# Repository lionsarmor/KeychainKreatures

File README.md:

# Keychain Kreatures

An ESP32-S3 virtual-pet and small handheld-game hardware project, designed around a repairable through-hole main-board kit and a separate factory-assembled power board.

**Current hardware: main C.6 + power P.4. Engineering prototypes—not a tested, certified or production-ready toy.** Main is 96 × 105 × 1.6 mm; power is now 50 × 50 × 1.6 mm. The power board needs independent removable case supports; mounting patterns do not match. Physical component fit, battery/case selection, factory DFM approval and powered qualification remain open.

## Current projects and downloads

| Board | Editable KiCad 10 project | Five-prototype review package | Gerbers and drills |
|---|---|---|---|
| Main C.6 · 2 copper layers | [Open main project](KK_main_module/KK_main_module.kicad_pro) | [Full main ZIP](KK_main_module/manufacturing/KK_MAIN_C6_P4_PAIRING_5_PROTOTYPE_REVIEW_2026-09-12.zip) | [Main fabrication ZIP](KK_main_module/manufacturing/KK_MAIN_C6_P4_PAIRING_GERBERS.zip) |
| Power P.4 · 4 copper layers | [Open power project](KK_power_module/KK_power_module.kicad_pro) | [Full power ZIP](KK_power_module/manufacturing/KK_POWER_P4_5_PROTOTYPE_REVIEW_2026-09-12.zip) | [Power fabrication ZIP](KK_power_module/manufacturing/KK_POWER_P4_GERBERS.zip) |

Download the repository or a **full review ZIP** to open a project with its local libraries, models and documentation. Install the KiCad 10 standard footprint and 3D libraries as well. For GitHub ZIP downloads, use the file page's download/raw action. The full review packages include fabrication files, BOMs, placement and test-point maps, schematic/assembly PDFs, source CAD, datasheets and verification evidence. The separate fabrication ZIPs do not replace the assembler's full review package.

[Start here](START_HERE.md) · [Documentation index](docs/README.md) · [Release notes](CHANGELOG.md) · [Release hashes](docs/CURRENT_RELEASE_INDEX.json)

Ordering the five engineering samples? Use the [PCBWay step-by-step submission folder](PCBWay/README.md): separate main/power Gerber uploads, power BOM/centroid, DFM questions, approval checklist and delivery/testing documents. This is a local preparation packet, not an order or manufacturing approval.

## Hardware in this revision

- Socketed **ESP32-S3 SuperMini**. Confirm the delivered seller revision, pinout and actual flash/PSRAM; do not infer N16R8 specifications from the SuperMini name.
- Existing ST7789V2 screen in landscape, **280 × 240 pixels**, and a separate socketed 3.3 V microSD reader. SD storage is not extra executable RAM.
- Nine soft controls: D-pad left, four action buttons right, one center function button, all below the screen. MCP23017 GPIO expansion.
- PWM audio with a TDA2822L amplifier, speaker connector and switched amplifier supply; vibration motor output with suppression.
- TSAL6200 infrared transmitter and TSOP38238 receiver, aimed toward the case opening. No sub-GHz radio.
- Separate socketed common-anode RGB LED and TLC5916 driver.
- Main board: **98 fitted through-hole positions**, all **43 resistors horizontal**, ten horizontal low-profile electrolytics, six flat-mounted TO-92 devices, removable IC/module sockets, JST connectors and **25 bare debug holes**.
- Power board: **108 fitted positions**, 28 rear test pads, USB-C charging input, battery protection, temperature interlock and three regulated output rails. This board is a **factory SMT subassembly**, not a student SMT soldering exercise.

All fitted electrical positions have resolving 3D model links. Some module and connector envelopes remain provisional; model coverage does not prove fit. Sockets, buttons and optical components necessarily retain height. The previous common-hole 20 mm spacer plan is superseded. Power placement, antenna clearance and independent support heights need a physical mock-up.

## Assembly and first power-up

New to electronics, or investigating a board that will not start? Use the [board-by-board troubleshooting guides and recording sheets](docs/troubleshooting/README.md). Begin with safety and unpowered checks; power-module live tests need a qualified instructor.

Read these before buying parts, soldering or powering a board:

1. [Main BOM and assembly/wiring guide](KK_main_module/assembly/ASSEMBLY_GUIDE.md), [reference BOM](KK_main_module/assembly/C6_BOM_BY_REFERENCE.csv), and [complete paired-kit extras](KK_main_module/assembly/C6_COMPLETE_KIT_EXTRAS.csv). Extras cover sockets, modules, mating plugs, wiring and provisional hardware; count them once per main+power pair.
2. [Print the stack review at actual size](docs/C6_P4_MECHANICAL_REVIEW.pdf), [front fit sheet](KK_main_module/assembly/C6_front_FIT_100_PERCENT.pdf) and [rear fit sheet](KK_main_module/assembly/C6_back_FIT_100_PERCENT.pdf). Measure the calibration line and dry-fit actual parts and plugged harnesses.
3. [Power fabrication/assembly requirements](KK_power_module/FABRICATION_REQUIREMENTS.md). Obtain manufacturer approval of the 0.4 mm WCSP, fine-pitch packages and **filled/capped/planarized via-in-pad** process. Ordinary via tenting is not equivalent.
4. [Power electrical review and current-limited first-power-up procedure](KK_power_module/assembly/P4_REVIEW_AND_TEST.md). Qualify power independently before attaching the populated main board. Real-cell testing requires a selected, documented cell and bonded thermistor.

Power **J3 → main J1**, keyed pin-for-pin:

| Pin | Rail |
|---|---|
| 1 | MCU_5V |
| 2 | GND |
| 3 | LOGIC_3V3 |
| 4 | ACT_3V2 |

**Never connect raw battery voltage to main J1. Power TP3/BAT_NEG is not TP4/GND; do not bypass battery protection with test-equipment grounds. Neither speaker output is ground.**

Charger USB carries **no data** to the ESP32. Do not combine ESP32 USB power and external main rails until exact-module reverse-feed behavior is qualified. Program the removable MCU separately for recovery. USB-A/default charging is deliberately slow and may not cover a running toy's load.

## Verification and remaining work

The issued C.6/P.4 sources passed fresh native ERC/DRC, connectivity and schematic-parity checks with **zero reported violations or opens**. [Static audit](docs/CURRENT_STATIC_AUDIT.json), [individual outline/hole audit](docs/CURRENT_STATIC_AUDIT.json) and package manifests identify exactly what was checked. Existing ignored-check settings are included in the native reports; clean reports are not a claim that every possible check was performed.

Run this lightweight saved-release consistency check from the repository root:

```sh
node tools/check_project.mjs
```

It verifies current source/package hashes, local assets, saved netlists and the inter-board interface. It does **not** rerun KiCad checks or simulate the circuit. See [tool instructions](tools/README.md) before running anything else. Do not rerun historical placement/route generators on finished CAD.

Remaining qualification includes physical socket/plug/case fit, battery/NTC selection, speaker power rating, simultaneous-load capacity, capacitor transient/ripple behavior, regulator/charger temperatures, USB behavior, rail sequencing, GPIO back-powering, RF performance and applicable product safety/EMC review. In particular, the older main 3.3 V reservation was 0.5 A while power screening used 0.4 A; reconcile measured peak demand and margin before approving the complete toy. Screening targets are not measured ratings.

## Firmware status

The planned virtual pet, games/apps, browser/Wi-Fi uploads, trading, save recovery and OTA workflow are **not implemented or validated by this hardware release**. Follow the current schematic and assembly guide for bring-up firmware. The historical ESP32-C3/MAX98357A/PCF8574 test sketch from earlier Git history is not compatible with this S3/MCP23017/TDA2822L board and must not be used as its factory test.

## History, contributions and licensing

The files directly inside **KK_main_module are now C.6**, and those directly inside **KK_power_module are P.4**. Older C.5/P.2 projects, intermediate routes, obsolete documents and one-off generators have been moved into [the cleanup archive](revisions/2026-09-12_current_only/). Use [revisions](revisions/README.md) for recovery; archived reports retain their original findings and are not current instructions. See [contribution guidance](CONTRIBUTING.md).

The project is intended for open development, but a project-wide license has **not yet been selected**. The OSHW silkscreen logo is not a certification or a substitute for license terms. Third-party KiCad assets and manufacturer documents retain their respective terms; do not assume this repository relicenses them. Thanks to the KiCad, Espressif and component-library communities.

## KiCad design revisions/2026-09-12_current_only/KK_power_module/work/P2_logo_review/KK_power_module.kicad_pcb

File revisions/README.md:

# Historical revisions — do not manufacture from here

The [2026-09-11 cleanup archive](2026-09-11_cleanup/) preserves the original relative project paths. No archived design is the current project.

- `KK_power_module/`: legacy two-wire power board, P.1, previous backups, old fabrication outputs and original engineering scripts.
- `KK_power_module/P2_compact/`: abandoned P.2 routing candidates and intermediate board snapshots. These routes were not imported or qualified.
- `KK_main_module/`: superseded reports, BOMs, routing candidates, older schematic capture, backups and former archives.

The current projects remain outside this directory; open them through [START_HERE.md](../START_HERE.md).

## Current-only folder cleanup

[2026-09-12_current_only](2026-09-12_current_only/) holds the former C.5 main root, C5_relayout, P2_compact, old main assembly/component investigations, intermediate C.6 routes, historical documents and one-off generators. [MOVE_MANIFEST.json](2026-09-12_current_only/MOVE_MANIFEST.json) records each move and protected current CAD/ZIP hashes. Active C.6/P.3 now sit directly in their module folders.

Archived relative compatibility symlinks preserve their original text and may not resolve from their new archive location. Recover a historical project into a separate scratch tree using the manifest; do not copy it over current CAD. No material content was deleted.

## C.6 / P.3 release archive

[2026-09-12_C6_P3_release](2026-09-12_C6_P3_release/) preserves the superseded C.5/P.2 manufacturing directories, ZIPs and reports, plus the previous Desktop print sheet and the C.6/P.3 preflight ZIPs before final documentation cleanup. None of those ZIPs is the current release. [MOVE_MANIFEST.json](2026-09-12_C6_P3_release/MOVE_MANIFEST.json) distinguishes moves from preserved copies and records exact hashes. No baseline CAD was deleted or overwritten.

## Recovery

[MOVE_MANIFEST.json](2026-09-11_cleanup/MOVE_MANIFEST.json) records each original path, new path and per-file SHA-256 hash. Every move was verified. Active CAD/library/model hashes were checked separately to establish that cleanup did not modify them. Nothing was deleted.

For recovery, copy the desired archived files to a **separate scratch project**, preserving their recorded original relative paths. Include corresponding libraries/models and any generator inputs. Do not overwrite the current projects. Archived generation scripts retain original paths and are historical source, not working commands in their relocated tree. Never run them over current CAD.

The former compatibility symlinks at `KK_main_module/archive`, `KK_main_module/pcb/backups` and `KK_main_module/schematic` are now archived too. Historical reports may contain obsolete links; the move manifests, not the old links, are the recovery map.

The archive may contain packages named `FACTORY` or `release`. Those names are historical and do not approve them for the present main board, battery or product.

## Compact power P.4

See [2026-09-12_power_compact](2026-09-12_power_compact/) for the preserved P.3 projects, prior packages, source snapshots and promotion hash map. Current power is 50 × 50 mm with separate mounts; main C.6 remains unchanged.

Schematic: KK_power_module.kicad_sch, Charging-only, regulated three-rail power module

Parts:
C1, C71, C72: 1u; C_0603_1608Metric; MPN GRM188R71C105KA12D
C2, C6, C9, C25, C35, C45, C51, C60, C70: 100n; C_0603_1608Metric; MPN GRM188R71C104KA01D
C3: 4.7u; C_0805_2012Metric; MPN GRM21BR71C475KA73L
C4, C20, C21, C30, C31, C40, C41: 10u; C_0805_2012Metric; MPN GRM21BR61C106KE15L
C5, C8, C22, C23, C24, C32, C33, C34, C42, C43, C44: 22u; C_0805_2012Metric; MPN GRM21BR61C226ME44L
C7, C52, C53, C54: 10n; C_0603_1608Metric; MPN GRM188R71H103KA01D
C28, C38, C48: 10p; C_0603_1608Metric; MPN GRM1885C1H100JA01D
D1: SMAJ5.0A; D_SMA; MPN SMAJ5.0A
F1: 4A FAST; Fuse_1206_3216Metric; MPN 0451004.MRL
J1: USB-C CHARGE ONLY; USB_C_HCTL; MPN HC-TYPE-C-16P-01A
J2: 1S CELL / VH; JST_VH_B2P-VH_1x02_P3.96mm_Vertical; MPN B2P-VH(LF)(SN)
J3: C.5 SYS_IN / XH; JST_XH_B4B-XH-A_1x04_P2.50mm_Vertical; MPN B4B-XH-A(LF)(SN)
J4: BATTERY NTC; JST_PH_B2B-PH-K_1x02_P2.00mm_Vertical; MPN B2B-PH-K-S(LF)(SN)
L1, L2, L3: 1uH; L_Coilcraft_XxL4020; MPN XFL4020-102MEC
LED1: POWER GOOD; LED_1206_3216Metric; MPN APT3216LZGCK
LED2: CHARGING; LED_1206_3216Metric; MPN APT3216SURCK
Q1, Q2, Q3: FS8205; MPN FS8205
Q4, Q5: AO3400A; SOT-23; MPN AO3400A
R1: 887k; R_0603_1608Metric; MPN RC0603FR07887KL
R2, R6, R7: 4.7k; R_0603_1608Metric; MPN RC0603FR074K7L
R3, R14, R60: 10k; R_0603_1608Metric; MPN RC0603FR0710KL
R4: 2.94k; R_0603_1608Metric; MPN RT0603BRD072K94L
R5: 1.3k; R_0603_1608Metric; MPN RC0603FR071K3L
R8: 470; R_0603_1608Metric; MPN RC0603FR07470RL
R9: 1k; R_0603_1608Metric; MPN RC0603FR071KL
R10: 182k; R_0603_1608Metric; MPN RT0603BRD07182KL
R11, R31, R41, R62, R64, R66: 100k; R_0603_1608Metric; MPN RT0603BRD07100KL
R12: 620; R_0603_1608Metric; MPN RC0603FR07620RL
R13, R51, R72, R73: 100k; R_0603_1608Metric; MPN RC0603FR07100KL
R20: 909k; R_0603_1608Metric; MPN RT0603BRD07909KL
R21: 101k; R_0603_1608Metric; MPN RT0603BRD07101KL
R30: 560k; R_0603_1608Metric; MPN RT0603BRD07560KL
R40, R43: 270k; R_0603_1608Metric; MPN RT0603BRD07270KL
R50: 470k; R_0603_1608Metric; MPN RC0603FR07470KL
R52, R53, R54: 100; R_0603_1608Metric; MPN RC0603FR07100RL
R61: 1060k; R_0603_1608Metric; MPN RT0603BRD071M06L
R63: 665k; R_0603_1608Metric; MPN RT0603BRD07665KL
R65: 649k; R_0603_1608Metric; MPN RT0603BRD07649KL
R70: 19.2k; R_0603_1608Metric; MPN RT0603BRD0719K2L
R71: 634; R_0603_1608Metric; MPN RT0603BRD07634RL
R74: 31.6k; R_0603_1608Metric; MPN RT0603BRD0731K6L
R75: 20k; R_0603_1608Metric; MPN RT0603BRD0720KL
SW1: OFF / ON; SW_SPDT_CK_JS102011SAQN; MPN JS102011SAQN
TP1: VBUS; TestPoint_Pad_D1.5mm; MPN BARE PCB PAD
TP2: VBAT; TestPoint_Pad_D1.5mm; MPN BARE PCB PAD
TP3: BAT_NEG; TestPoint_Pad_D1.5mm; MPN BARE PCB PAD
TP4: GND; TestPoint_Pad_D1.5mm; MPN BARE PCB PAD
TP5: SYS_RAW; TestPoint_Pad_D1.5mm; MPN BARE PCB PAD
TP6: SYS_SW; TestPoint_Pad_D1.5mm; MPN BARE PCB PAD
TP7: RUN_CTL; TestPoint_Pad_D1.5mm; MPN BARE PCB PAD
TP8: EF_UVLO; TestPoint_Pad_D1.5mm; MPN BARE PCB PAD
TP9: EF_ILIM; TestPoint_Pad_D1.5mm; MPN BARE PCB PAD
TP10: EF_FAULT_N; TestPoint_Pad_D1.5mm; MPN BARE PCB PAD
TP11: PG_ALL; TestPoint_Pad_D1.5mm; MPN BARE PCB PAD
TP12: RAILS_EN; TestPoint_Pad_D1.5mm; MPN BARE PCB PAD
TP13: REG_5V; TestPoint_Pad_D1.5mm; MPN BARE PCB PAD
TP14: REG_3V3; TestPoint_Pad_D1.5mm; MPN BARE PCB PAD
TP15: REG_3V2; TestPoint_Pad_D1.5mm; MPN BARE PCB PAD
TP16: MCU_5V; TestPoint_Pad_D1.5mm; MPN BARE PCB PAD
TP17: LOGIC_3V3; TestPoint_Pad_D1.5mm; MPN BARE PCB PAD
TP18: ACT_3V2; TestPoint_Pad_D1.5mm; MPN BARE PCB PAD
TP19: NTC; TestPoint_Pad_D1.5mm; MPN BARE PCB PAD
TP20: CC_DEFAULT_N; TestPoint_Pad_D1.5mm; MPN BARE PCB PAD
TP21: USB_HIGH_CURRENT; TestPoint_Pad_D1.5mm; MPN BARE PCB PAD
TP22: USB_CHG; TestPoint_Pad_D1.5mm; MPN BARE PCB PAD
TP23: USB_PORT_ILIM; TestPoint_Pad_D1.5mm; MPN BARE PCB PAD
TP24: USB_LIMIT_FAULT_N; TestPoint_Pad_D1.5mm; MPN BARE PCB PAD
TP25: CC_3V3; TestPoint_Pad_D1.5mm; MPN BARE PCB PAD
TP26: PGOOD_N; TestPoint_Pad_D1.5mm; MPN BARE PCB PAD
TP27: CHARGE_N; TestPoint_Pad_D1.5mm; MPN BARE PCB PAD
TP28: VOLTAGES_OK; TestPoint_Pad_D1.5mm; MPN BARE PCB PAD
U1: BQ24075TRGTR; VQFN-16-1EP_3x3mm_P0.5mm_EP1.6x1.6mm; MPN BQ24075TRGTR
U2: DW01A / H&M; SOT-23-6; MPN DW01A
U3: TUSB320LAIRWBR; Texas_X2QFN-12_1.6x1.6mm_P0.4mm; MPN TUSB320LAIRWBR
U4: TPS259530DSGR; Texas_DSG0008A_WSON-8-1EP_2x2mm_P0.5mm_EP0.9x1.6mm; MPN TPS259530DSGR
U5, U6, U7: TPS63060DSCR; Texas_S-PWSON-N10; MPN TPS63060DSCR
U8, U9, U10: TPS22918DBVR; SOT-23-6; MPN TPS22918DBVR
U11: SN74AUP1G17DBVR; SOT-23-5; MPN SN74AUP1G17DBVR
U12: TPS386000RGPR; Texas_RGP0020D_VQFN-20-1EP_4x4mm_P0.5mm_EP2.7x2.7mm; MPN TPS386000RGPR
U13: TPS22950YBHR; TPS22950_YBH; MPN TPS22950YBHR
U14: TLV75533PDBVR; SOT-23-5; MPN TLV75533PDBVR

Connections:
/ACT_3V2: J3.4 (3V2), R54.1, TP18.1, U10.6 (VOUT)
/BAT_NEG: C6.2, J2.2 (CELL-), Q1.1 (S1), Q2.1 (S1), Q3.1 (S1), TP3.1, U2.6 (GND)
/CC1: J1.A5 (CC1), U3.1 (CC1)
/CC2: J1.B5 (CC2), U3.2 (CC2)
/CC_3V3: C2.1, C72.1, R2.1, R3.1, TP25.1, U3.12 (VDD), U14.5 (OUT)
/CC_DEFAULT_N: Q4.1 (G), R2.2, TP20.1, U3.7 (OUT1)
/CELL_PLUS: F1.1, J2.1 (CELL+)
/CHARGE_N: R7.2, TP27.1, U1.9 (~CHG)
/CHG_ILIM: R5.1, U1.12 (ILIM)
/CHG_ISET: R4.1, U1.16 (ISET)
/DRAIN_COMMON: Q1.2 (D1), Q1.5 (D2), Q2.2 (D1), Q2.5 (D2), Q3.2 (D1), Q3.5 (D2)
/EF_FAULT_N: R13.2, TP10.1, U4.6 (FAULT_N)
/EF_ILIM: R12.1, TP9.1, U4.7 (ILM)
/EF_SLEW: C7.1, U4.1 (dVdt)
/EF_UVLO: R10.2, R11.1, TP8.1, U4.2 (EN / UVLO)
/GND: C1.2, C2.2, C3.2, C4.2, C5.2, C7.2, C8.2, C9.2, C20.2, C21.2, C22.2, C23.2, C24.2, C25.2, C28.2, C30.2, C31.2, C32.2, C33.2, C34.2, C35.2, C38.2, C40.2, C41.2, C42.2, C43.2, C44.2, C45.2, C48.2, C51.2, C52.2, C53.2, C54.2, C60.2, C70.2, C71.2, C72.2, D1.2 (A), J1.A1 (GND), J1.A12 (GND), J1.B1 (GND), J1.B12 (GND), J1.S1 (SHIELD), J3.2 (GND), J4.2 (GND), Q1.3 (S2), Q2.3 (S2), Q3.3 (S2), Q4.2 (S), Q5.2 (S), R4.2, R5.2, R9.1, R11.2, R12.2, R21.2, R31.2, R41.2, R51.2, R62.2, R64.2, R66.2, R70.2, R72.2, R75.2, SW1.1 (A), TP4.1, U1.4 (~CE), U1.6 (EN1), U1.8 (VSS), U1.15 (SYSOFF), U1.17 (VSS), U3.3 (PORT = SINK), U3.10 (GND), U3.11 (EN_N), U4.8 (GND), U4.9 (EP / GND), U5.7 (GND), U5.11 (PGND), U6.7 (GND), U6.11 (PGND), U7.7 (GND), U7.11 (PGND), U8.2 (GND), U9.2 (GND), U10.2 (GND), U11.3 (GND), U12.6 (SENSE4H), U12.11 (NC / GND), U12.12 (GND), U12.20 (WDI), U12.21 (EP / GND), U13.C1 (GND), U14.2 (GND)
/LED1_K: LED1.1 (K), R6.1
/LED2_K: LED2.1 (K), R7.1
/LOGIC_3V3: J3.3 (3V3), R53.1, TP17.1, U9.6 (VOUT)
/MCU_5V: J3.1 (5V), R52.1, TP16.1, U8.6 (VOUT)
/NTC: J4.1 (NTC), R74.2, R75.1, TP19.1, U1.1 (TS)
/OC: Q1.4 (G2 / OC), Q2.4 (G2 / OC), Q3.4 (G2 / OC), U2.3 (OC)
/OD: Q1.6 (G1 / OD), Q2.6 (G1 / OD), Q3.6 (G1 / OD), U2.1 (OD)
/PGOOD_N: R6.2, TP26.1, U1.7 (~PGOOD)
/PG_ALL: R50.2, TP11.1, U5.5 (PG), U6.5 (PG), U7.5 (PG)
/PROTECT_CS: R9.2, U2.2 (CS)
/PROTECT_VCC: C6.1, R8.2, U2.5 (VCC)
/RAILS_EN: R51.1, TP12.1, U8.3 (ON), U9.3 (ON), U10.3 (ON), U11.4 (Y)
/REG_3V2: C42.1, C43.1, C44.1, R40.1, R65.1, TP15.1, U7.9 (VOUT), U10.1 (VIN)
/REG_3V3: C32.1, C33.1, C34.1, C51.1, R30.1, R50.1, R60.1, R63.1, TP14.1, U6.9 (VOUT), U9.1 (VIN), U11.5 (VCC)
/REG_5V: C22.1, C23.1, C24.1, R20.1, R61.1, TP13.1, U5.9 (VOUT), U8.1 (VIN)
/REG_ENABLE: R14.2, U5.3 (EN), U5.4 (PS/SYNC), U6.3 (EN), U6.4 (PS/SYNC), U7.3 (EN), U7.4 (PS/SYNC)
/RUN_CTL: R10.1, R14.1, SW1.2 (B), TP7.1, U12.1 (MR_N)
/SENSE_3V2: R65.2, R66.1, U12.8 (SENSE3)
/SENSE_3V3: R63.2, R64.1, U12.9 (SENSE2)
/SENSE_5V: R61.2, R62.1, U12.10 (SENSE1)
/SYS_RAW: C5.1, C9.1, C60.1, R13.1, SW1.3 (C), TP5.1, U1.10 (OUT), U1.11 (OUT), U4.3 (IN), U4.4 (IN), U12.14 (VDD)
/SYS_SW: C8.1, C20.1, C21.1, C30.1, C31.1, C40.1, C41.1, TP6.1, U4.5 (OUT), U5.2 (VIN), U6.2 (VIN), U7.2 (VIN), U12.7 (SENSE4L)
/U5_AUX: C25.1, U5.6 (VAUX)
/U5_FB: C28.1, R20.2, R21.1, U5.8 (FB)
/U5_L1: L1.1, U5.1 (L1)
/U5_L2: L1.2, U5.10 (L2)
/U6_AUX: C35.1, U6.6 (VAUX)
/U6_FB: C38.1, R30.2, R31.1, U6.8 (FB)
/U6_L1: L2.1, U6.1 (L1)
/U6_L2: L2.2, U6.10 (L2)
/U7_AUX: C45.1, U7.6 (VAUX)
/U7_FB: C48.1, R41.1, R43.2, U7.8 (FB)
/U7_FB_MID: R40.2, R43.1
/U7_L1: L3.1, U7.1 (L1)
/U7_L2: L3.2, U7.10 (L2)
/U8_CT: C52.1, U8.4 (CT)
/U8_QOD: R52.2, U8.5 (QOD)
/U9_CT: C53.1, U9.4 (CT)
/U9_QOD: R53.2, U9.5 (QOD)
/U10_CT: C54.1, U10.4 (CT)
/U10_QOD: R54.2, U10.5 (QOD)
/USB_CHG: C3.1, C71.1, R74.1, TP22.1, U1.13 (IN), U13.B2 (VOUT)
/USB_HIGH_CURRENT: Q4.3 (D), Q5.1 (G), R3.2, R72.1, TP21.1, U1.5 (EN2)
/USB_LIMIT_FAULT_N: R73.2, TP24.1, U13.A2 (FLT_N)
/USB_PORT_ILIM: R70.1, R71.1, TP23.1, U13.C2 (ILIM)
/USB_PORT_ILIM_FAST: Q5.3 (D), R71.2
/VBAT: C4.1, F1.2, R8.1, TP2.1, U1.2 (BAT), U1.3 (BAT)
/VBUS: C1.1, C70.1, D1.1 (K), J1.A4 (VBUS), J1.A9 (VBUS), J1.B4 (VBUS), J1.B9 (VBUS), LED1.2 (A), LED2.2 (A), R1.1, R73.1, TP1.1, U13.A1 (ON), U13.B1 (VIN), U14.1 (IN), U14.3 (EN)
/VBUS_DET: R1.2, U3.4 (VBUS_DET)
/VOLTAGES_OK: R60.2, TP28.1, U11.2 (A), U12.15 (RESET1_N), U12.16 (RESET2_N), U12.17 (RESET3_N)

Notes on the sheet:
USB-C CHARGING ONLY
CELL CHARGER / POWER PATH
CELL PROTECTION / FUSE
SYSTEM SWITCH / INRUSH / UVLO
5 V BUCK-BOOST
3.3 V BUCK-BOOST
3.2 V BUCK-BOOST
ALL-RAIL READY / SOFT OUTPUTS
VOLTAGE SUPERVISION / STARTUP
USB-A / USB-C INPUT CURRENT
MAIN BOARD HARNESS / DEBUG
KEYCHAIN KREATURES / POWER P.2 - ENGINEERING, NOT RELEASED

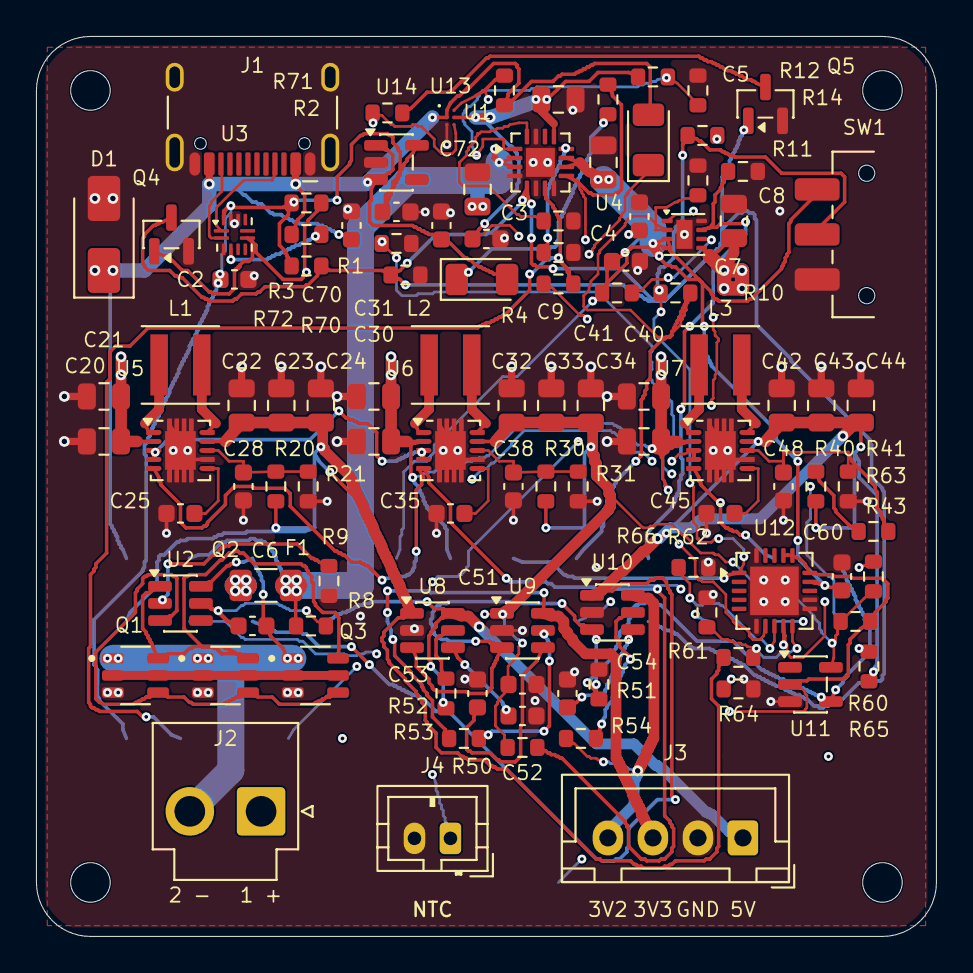
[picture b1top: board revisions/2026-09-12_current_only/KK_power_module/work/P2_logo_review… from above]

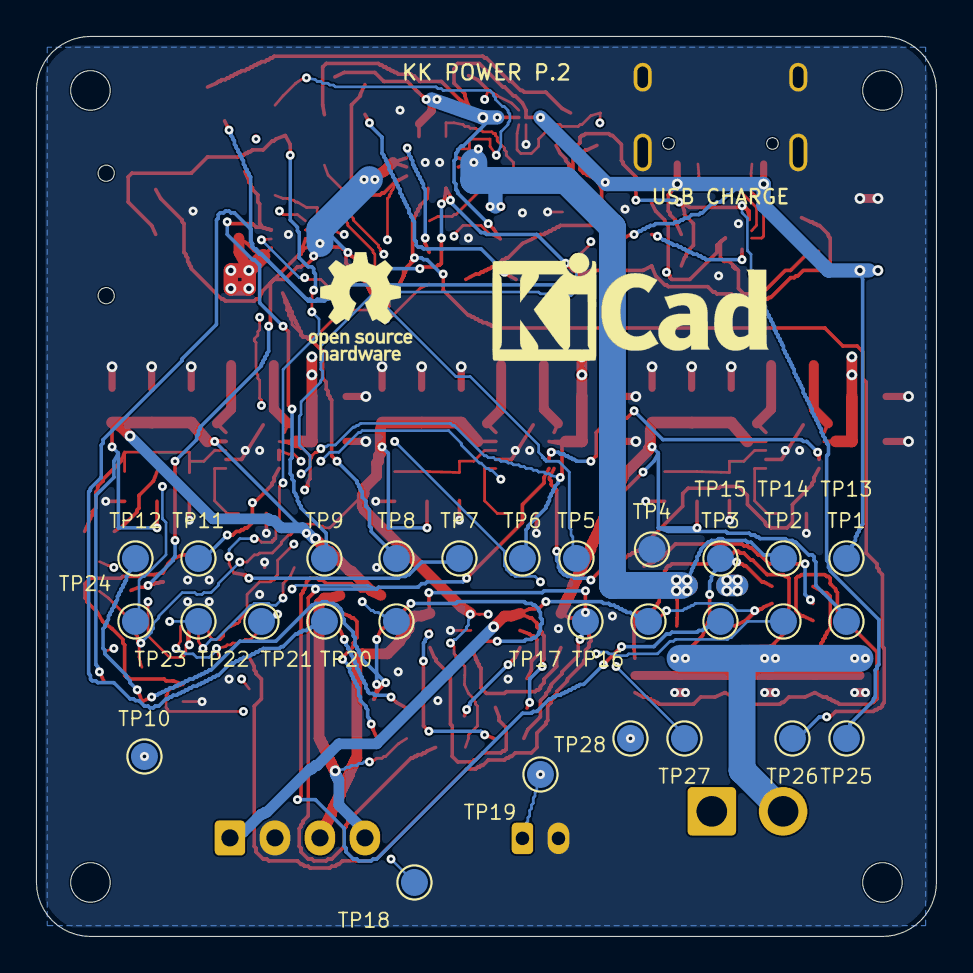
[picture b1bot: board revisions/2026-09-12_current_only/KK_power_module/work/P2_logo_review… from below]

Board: 4 copper layers, 50.0 x 50.0 mm, 142 parts (30 on the bottom side), 66 nets.

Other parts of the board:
H1, H2, H3, H4: MountingHole_2.2mm_M2
LOGO1: KiCad-Logo_6mm_SilkScreen
LOGO2: OSHW-Logo_5.7x6mm_SilkScreen

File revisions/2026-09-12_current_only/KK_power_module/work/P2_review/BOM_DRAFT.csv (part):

Reference,Value,Candidate MPN - purchasing audit pending,Footprint,Group,Datasheet,Notes
J1,USB-C CHARGE ONLY,HC-TYPE-C-16P-01A,KK_Power:USB_C_HCTL,USB-C CHARGING ONLY,https://datasheet.lcsc.com/lcsc/2211161000_HCTL-HC-TYPE-C-16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,All USB D+/D- and SBU pins intentionally NC. Shield grounded.
U14,TLV75533PDBVR,TLV75533PDBVR,KK_Power:SOT-23-5,USB-C CHARGING ONLY,https://www.ti.com/lit/ds/symlink/tlv755p.pdf,"Dedicated USB-powered CC supply: TUSB320 VDD recommended maximum is 5V, so do not feed it raw USB. Not connected to main-board 3V3."
C72,1u,GRM188R71C105KA12D,KK_Power:C_0603_1608Metric,USB-C CHARGING ONLY,,Check effective capacitance at operating bias; 16V minimum for bulk.
U3,TUSB320LAIRWBR,TUSB320LAIRWBR,KK_Power:Texas_X2QFN-12_1.6x1.6mm_P0.4mm,USB-C CHARGING ONLY,https://www.ti.com/lit/ds/symlink/tusb320lai.pdf,Sink/GPIO mode; internal Rd. Pullups use the same regulated supply to avoid backpowering. Not a USB data controller.
R1,887k,RC0603FR07887KL,KK_Power:R_0603_1608Metric,USB-C CHARGING ONLY,,"1%; standard E96 value. TUSB320LAI rev D recommended VBUS resistor range 855..920kohm, nominal 887kohm."
R2,4.7k,RC0603FR074K7L,KK_Power:R_0603_1608Metric,USB-C CHARGING ONLY,,1% thick film
Q4,AO3400A,AO3400A,KK_Power:SOT-23,USB-C CHARGING ONLY,https://www.aosmd.com/sites/default/files/res/datasheets/AO3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,Logic-level FET specified at 2.5V gate drive; clamps high-current request in default/unattached state.
R3,10k,RC0603FR0710KL,KK_Power:R_0603_1608Metric,USB-C CHARGING ONLY,,1% thick film
C1,1u,GRM188R71C105KA12D,KK_Power:C_0603_1608Metric,USB-C CHARGING ONLY,,Check effective capacitance at operating bias; 16V minimum for bulk.
C2,100n,GRM188R71C104KA01D,KK_Power:C_0603_1608Metric,USB-C CHARGING ONLY,,Check effective capacitance at operating bias; 16V minimum for bulk.
D1,SMAJ5.0A,SMAJ5.0A,KK_Power:D_SMA,USB-C CHARGING ONLY,,Unidirectional input TVS; pin 1 cathode.
U1,BQ24075TRGTR,BQ24075TRGTR,KK_Power:VQFN-16-1EP_3x3mm_P0.5mm_EP1.6x1.6mm,CELL CHARGER / POWER PATH,https://www.ti.com/lit/ds/symlink/bq24075t.pdf,Voltage-based TS network; only the T variant is valid. SYSOFF pin 15 grounded. Approx. 300mA charge target. No NTC bypass.
R4,2.94k,RT0603BRD072K94L,KK_Power:R_0603_1608Metric,CELL CHARGER / POWER PATH,,0.1%; below the 3kohm maximum programming resistance including tolerance.
R5,1.3k,RC0603FR071K3L,KK_Power:R_0603_1608Metric,CELL CHARGER / POWER PATH,,1% thick film
C3,4.7u,GRM21BR71C475KA73L,KK_Power:C_0805_2012Metric,CELL CHARGER / POWER PATH,,Check effective capacitance at operating bias; 16V minimum for bulk.
C4,10u,GRM21BR61C106KE15L,KK_Power:C_0805_2012Metric,CELL CHARGER / POWER PATH,,Check effective capacitance at operating bias; 16V minimum for bulk.
C5,22u,GRM21BR61C226ME44L,KK_Power:C_0805_2012Metric,CELL CHARGER / POWER PATH,,Check effective capacitance at operating bias; 16V minimum for bulk.
J4,BATTERY NTC,B2B-PH-K-S(LF)(SN),KK_Power:JST_PH_B2B-PH-K_1x02_P2.00mm_Vertical,CELL CHARGER / POWER PATH,,10k NTC thermally bonded to cell. No fitted NO_NTC bypass.
LED1,POWER GOOD,APT3216LZGCK,KK_Power:LED_1206_3216Metric,CELL CHARGER / POWER PATH,,
R6,4.7k,RC0603FR074K7L,KK_Power:R_0603_1608Metric,CELL CHARGER / POWER PATH,,1% thick film
LED2,CHARGING,APT3216SURCK,KK_Power:LED_1206_3216Metric,CELL CHARGER / POWER PATH,,
R7,4.7k,RC0603FR074K7L,KK_Power:R_0603_1608Metric,CELL CHARGER / POWER PATH,,1% thick film
J2,1S CELL / VH,B2P-VH(LF)(SN),KK_Power:JST_VH_B2P-VH_1x02_P3.96mm_Vertical,CELL PROTECTION / FUSE,,Higher-current polarity-controlled cell harness. Requires a cell rated at least 4A continuous; not interchangeable with old PH or main-board XH harnesses.
F1,4A FAST,0451004.MRL,KK_Power:Fuse_1206_3216Metric,CELL PROTECTION / FUSE,,Secondary fault fuse; not a substitute for cell protection. Cell and fuse I-squared-t coordination still required.
U2,DW01A / H&M,DW01A,KK_Power:SOT-23-6,CELL PROTECTION / FUSE,https://hmsemi.com/downfile/DW01A.PDF,"H&M Semiconductor DW01A per linked manufacturer sheet. No generic substitutions. Parallel-FET trip thresholds, cell limits and fuse coordination remain release holds."
Q1,FS8205,FS8205,KK_Power:FS8205,CELL PROTECTION / FUSE,https://www.ic-fortune.com/upload/Download/FS8205-DS-19_EN.pdf,Three parallel matched dual-MOSFET banks. Must qualify current sharing and trip thresholds.
Q2,FS8205,FS8205,KK_Power:FS8205,CELL PROTECTION / FUSE,https://www.ic-fortune.com/upload/Download/FS8205-DS-19_EN.pdf,Three parallel matched dual-MOSFET banks. Must qualify current sharing and trip thresholds.
Q3,FS8205,FS8205,KK_Power:FS8205,CELL PROTECTION / FUSE,https://www.ic-fortune.com/upload/Download/FS8205-DS-19_EN.pdf,Three parallel matched dual-MOSFET banks. Must qualify current sharing and trip thresholds.
R8,470,RC0603FR07470RL,KK_Power:R_0603_1608Metric,CELL PROTECTION / FUSE,,1% thick film
R9,1k,RC0603FR071KL,KK_Power:R_0603_1608Metric,CELL PROTECTION / FUSE,,1% thick film
C6,100n,GRM188R71C104KA01D,KK_Power:C_0603_1608Metric,CELL PROTECTION / FUSE,,Check effective capacitance at operating bias; 16V minimum for bulk.
SW1,OFF / ON,JS102011SAQN,KK_Power:SW_SPDT_CK_JS102011SAQN,SYSTEM SWITCH / INRUSH / UVLO,https://www.ckswitches.com/media/1422/js.pdf,Signal-level switch only; charging remains on when toy off.
U4,TPS259530DSGR,TPS259530DSGR,KK_Power:Texas_DSG0008A_WSON-8-1EP_2x2mm_P0.5mm_EP0.9x1.6mm,SYSTEM SWITCH / INRUSH / UVLO,https://www.ti.com/lit/ds/symlink/tps2595.pdf,Latch-off on thermal fault; cycle switch to recover.
R10,182k,RT0603BRD07182KL,KK_Power:R_0603_1608Metric,SYSTEM SWITCH / INRUSH / UVLO,,0.1% thin film
R11,100k,RT0603BRD07100KL,KK_Power:R_0603_1608Metric,SYSTEM SWITCH / INRUSH / UVLO,,0.1% thin film
R12,620,RC0603FR07620RL,KK_Power:R_0603_1608Metric,SYSTEM SWITCH / INRUSH / UVLO,,1% thick film
C7,10n,GRM188R71H103KA01D,KK_Power:C_0603_1608Metric,SYSTEM SWITCH / INRUSH / UVLO,,Check effective capacitance at operating bias; 16V minimum for bulk.
C8,22u,GRM21BR61C226ME44L,KK_Power:C_0805_2012Metric,SYSTEM SWITCH / INRUSH / UVLO,,Check effective capacitance at operating bias; 16V minimum for bulk.
C9,100n,GRM188R71C104KA01D,KK_Power:C_0603_1608Metric,SYSTEM SWITCH / INRUSH / UVLO,,Check effective capacitance at operating bias; 16V minimum for bulk.
R13,100k,RC0603FR07100KL,KK_Power:R_0603_1608Metric,SYSTEM SWITCH / INRUSH / UVLO,,1% thick film
R14,10k,RC0603FR0710KL,KK_Power:R_0603_1608Metric,SYSTEM SWITCH / INRUSH / UVLO,,1% thick film
U5,TPS63060DSCR,TPS63060DSCR,KK_Power:Texas_S-PWSON-N10,5 V BUCK-BOOST,https://www.ti.com/lit/ds/symlink/tps63060.pdf,Forced PWM for controlled rail accuracy/ripple. PG shared open-drain.
L1,1uH,XFL4020-102MEC,KK_Power:L_Coilcraft_XxL4020,5 V BUCK-BOOST,https://www.coilcraft.com/getmedia/50632d43-da1b-4cdb-8ab4-3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,"TI-recommended family; 5.1A Isat at 20% loss, manufacturer limits apply."
C20,10u,GRM21BR61C106KE15L,KK_Power:C_0805_2012Metric,5 V BUCK-BOOST,,Check effective capacitance at operating bias; 16V minimum for bulk.
C21,10u,GRM21BR61C106KE15L,KK_Power:C_0805_2012Metric,5 V BUCK-BOOST,,Check effective capacitance at operating bias; 16V minimum for bulk.
C22,22u,GRM21BR61C226ME44L,KK_Power:C_0805_2012Metric,5 V BUCK-BOOST,,Check effective capacitance at operating bias; 16V minimum for bulk.
C23,22u,GRM21BR61C226ME44L,KK_Power:C_0805_2012Metric,5 V BUCK-BOOST,,Check effective capacitance at operating bias; 16V minimum for bulk.
C24,22u,GRM21BR61C226ME44L,KK_Power:C_0805_2012Metric,5 V BUCK-BOOST,,Check effective capacitance at operating bias; 16V minimum for bulk.
C25,100n,GRM188R71C104KA01D,KK_Power:C_0603_1608Metric,5 V BUCK-BOOST,,Check effective capacitance at operating bias; 16V minimum for bulk.
R20,909k,RT0603BRD07909KL,KK_Power:R_0603_1608Metric,5 V BUCK-BOOST,,0.1% thin film
R21,101k,RT0603BRD07101KL,KK_Power:R_0603_1608Metric,5 V BUCK-BOOST,,0.1% thin film
C28,10p,GRM1885C1H100JA01D,KK_Power:C_0603_1608Metric,5 V BUCK-BOOST,,"10pF across the lower feedback resistor per TPS63060 datasheet, not an upper-divider feedforward capacitor."
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
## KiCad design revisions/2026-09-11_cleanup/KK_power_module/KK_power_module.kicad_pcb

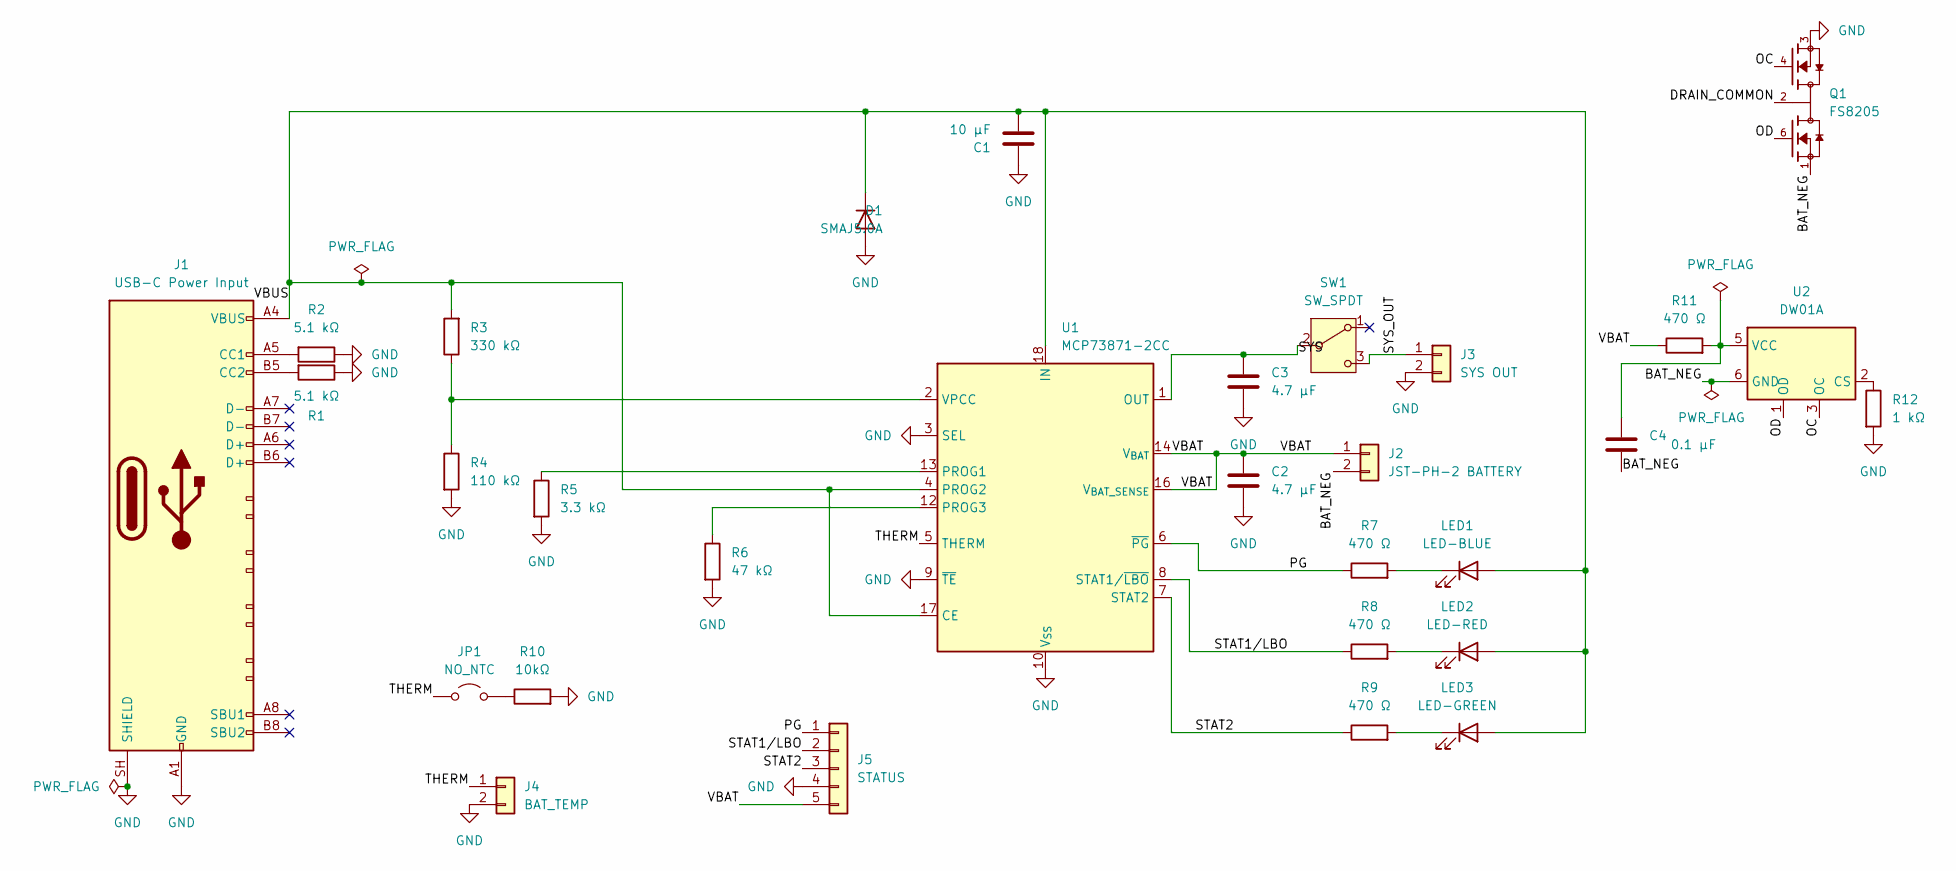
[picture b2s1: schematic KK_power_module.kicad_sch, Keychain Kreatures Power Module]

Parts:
C1: 10 µF; C_1206_3216Metric_Pad1.33x1.80mm_HandSolder
C2, C3: 4.7 µF; C_1206_3216Metric_Pad1.33x1.80mm_HandSolder
C4: 0.1 µF; C_1206_3216Metric_Pad1.33x1.80mm_HandSolder
D1: SMAJ5.0A; D_SMA_Handsoldering
J1: USB-C Power Input; USB_C_Receptacle_HCTL_HC-TYPE-C-16P-01A
J2: JST-PH-2 BATTERY; JST_PH_S2B-PH-K_1x02_P2.00mm_Horizontal
J3: SYS OUT; JST_PH_S2B-PH-K_1x02_P2.00mm_Horizontal
J4: BAT_TEMP; PinHeader_1x02_P2.54mm_Vertical
J5: STATUS; PinHeader_1x05_P2.54mm_Vertical
JP1: NO_NTC; PinHeader_1x02_P2.54mm_Vertical
LED1: LED-BLUE; LED_1206_3216Metric_Pad1.42x1.75mm_HandSolder
LED2: LED-RED; LED_1206_3216Metric_Pad1.42x1.75mm_HandSolder
LED3: LED-GREEN; LED_1206_3216Metric_Pad1.42x1.75mm_HandSolder
Q1: FS8205; SOT95P280X145-6N; PARTREV 1.9
R1, R2: 5.1 kΩ; R_1206_3216Metric_Pad1.30x1.75mm_HandSolder
R3: 330 kΩ; R_1206_3216Metric_Pad1.30x1.75mm_HandSolder
R4: 110 kΩ; R_1206_3216Metric_Pad1.30x1.75mm_HandSolder
R5: 3.3 kΩ; R_1206_3216Metric_Pad1.30x1.75mm_HandSolder
R6: 47 kΩ; R_1206_3216Metric_Pad1.30x1.75mm_HandSolder
R7, R8, R9, R11: 470 Ω; R_1206_3216Metric_Pad1.30x1.75mm_HandSolder
R10: 10kΩ; R_1206_3216Metric_Pad1.30x1.75mm_HandSolder
R12: 1 kΩ; R_1206_3216Metric_Pad1.30x1.75mm_HandSolder
SW1: SW_SPDT; SW_SPDT_CK_JS102011SAQN
U1: MCP73871-2CC; QFN-20-1EP_4x4mm_P0.5mm_EP2.5x2.5mm
U2: DW01A; SOT-23-6

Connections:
/BAT_NEG: C4.1, J2.2, Q1.1, U2.6 (GND)
/DRAIN_COMMON: Q1.2, Q1.5
/OC: Q1.4, U2.3 (OC)
/OD: Q1.6, U2.1 (OD)
/PG: J5.1, R7.1, U1.6 (~PG)
/STAT1/LBO: J5.2, R8.1, U1.8 (STAT1/~LBO)
/STAT2: J5.3, R9.1, U1.7 (STAT2)
/SYS: C3.1, SW1.2 (B), U1.1 (OUT), U1.20 (OUT)
/SYS_OUT: J3.1, SW1.3 (C)
/THERM: J4.1, JP1.1 (A), U1.5 (THERM)
/VBAT: C2.1, J2.1, J5.5, R11.1, U1.14 (V_{BAT}), U1.15 (V_{BAT}), U1.16 (V_{BAT_SENSE})
/VBUS: C1.2, D1.1 (K), J1.A4 (VBUS), J1.A9 (VBUS), J1.B4 (VBUS), J1.B9 (VBUS), LED1.2 (A), LED2.2 (A), LED3.2 (A), R3.2, U1.4 (PROG2), U1.17 (CE), U1.18 (IN), U1.19 (IN)
GND: C1.1, C2.2, C3.2, D1.2 (A), J1.A1 (GND), J1.A12 (GND), J1.B1 (GND), J1.B12 (GND), J1.SH (SHIELD), J3.2, J4.2, J5.4, Q1.3, R1.1, R2.1, R4.2, R5.2, R6.2, R10.2, R12.2, U1.3 (SEL), U1.9 (~TE), U1.10 (V_{SS}), U1.11 (V_{SS}), U1.21 (V_{SS})
unnamed: J1.A5 (CC1), R2.2
unnamed: J1.B5 (CC2), R1.2
unnamed: JP1.2 (B), R10.1
unnamed: LED1.1 (K), R7.2
unnamed: LED2.1 (K), R8.2
unnamed: LED3.1 (K), R9.2
unnamed: R5.1, U1.13 (PROG1)
unnamed: R6.1, U1.12 (PROG3)
unnamed: R3.1, R4.1, U1.2 (VPCC)
unnamed: R12.1, U2.2 (CS)
unnamed: C4.2, R11.2, U2.5 (VCC)

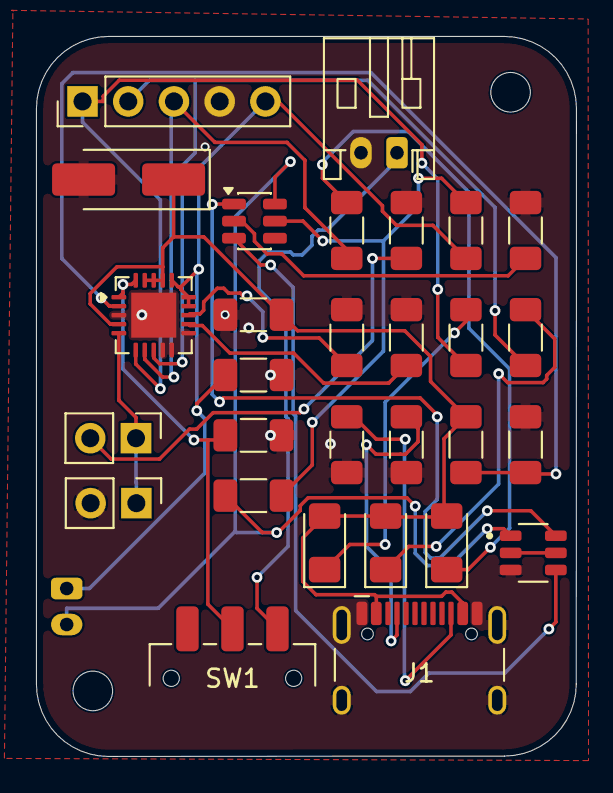
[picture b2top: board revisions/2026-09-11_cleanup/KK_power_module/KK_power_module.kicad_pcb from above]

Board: 2 copper layers, 30.0 x 40.0 mm, 32 parts (1 on the bottom side), 24 nets.

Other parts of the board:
H1, H2: MountingHole_2.2mm_M2
